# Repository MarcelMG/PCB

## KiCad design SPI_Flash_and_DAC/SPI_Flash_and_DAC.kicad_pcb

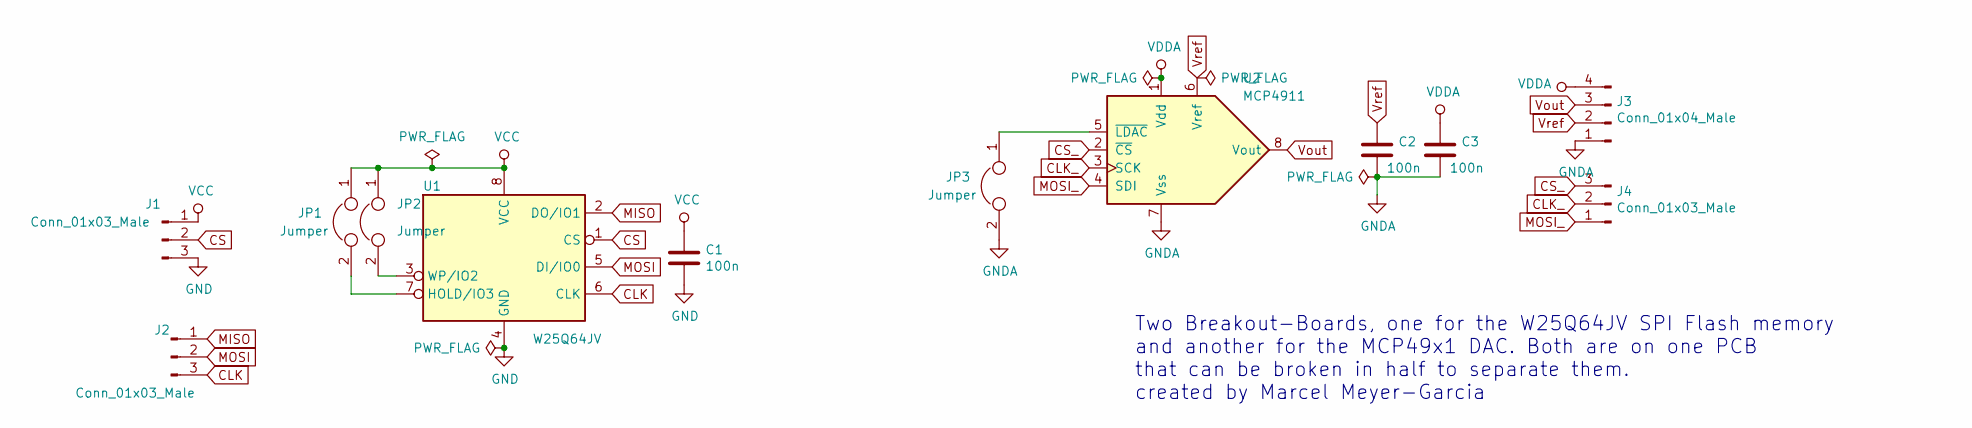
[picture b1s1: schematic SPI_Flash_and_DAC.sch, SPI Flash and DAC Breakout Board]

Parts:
C1, C2, C3: 100n; C_0805_2012Metric_Pad1.15x1.40mm_HandSolder
J1, J2, J4: Conn_01x03_Male; PinHeader_1x03_P2.54mm_Vertical
J3: Conn_01x04_Male; PinHeader_1x04_P2.54mm_Vertical
JP1, JP2, JP3: Jumper; SolderJumper-2_P1.3mm_Open_RoundedPad1.0x1.5mm
U1: W25Q64JV; SOIJ-8_5.3x5.3mm_P1.27mm
U2: MCP4911; SOIC-8_3.9x4.9mm_P1.27mm

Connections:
CLK: J2.3, U1.6 (CLK)
CLK_: J4.2, U2.3 (SCK)
CS: J1.2, U1.1 (CS)
CS_: J4.3, U2.2 (~CS)
GND: C1.2, J1.3, U1.4 (GND)
GNDA: C2.2, C3.2, J3.1, JP3.2, U2.7 (Vss)
MISO: J2.1, U1.2 (DO/IO1)
MOSI: J2.2, U1.5 (DI/IO0)
MOSI_: J4.1, U2.4 (SDI)
unnamed: JP1.2, U1.7 (HOLD/IO3)
unnamed: JP2.2, U1.3 (WP/IO2)
unnamed: JP3.1, U2.5 (~LDAC)
VCC: C1.1, J1.1, JP1.1, JP2.1, U1.8 (VCC)
VDDA: C3.1, J3.4, U2.1 (Vdd)
Vout: J3.3, U2.8 (Vout)
Vref: C2.1, J3.2, U2.6 (Vref)

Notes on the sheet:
Two Breakout-Boards, one for the W25Q64JV SPI Flash memory and another for the MCP49x1 DAC. Both are on one PCB that can be broken in half to separate them. created by Marcel Meyer-Garcia

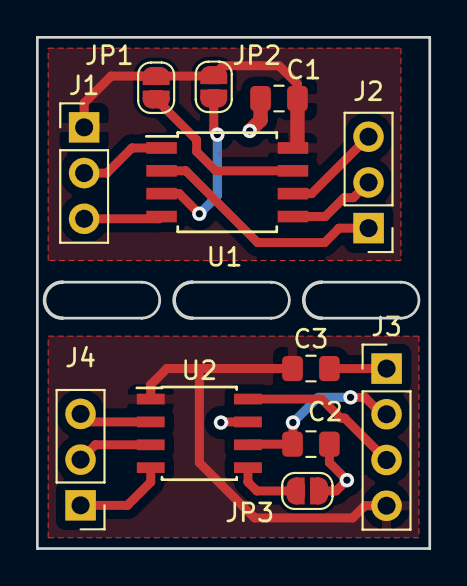
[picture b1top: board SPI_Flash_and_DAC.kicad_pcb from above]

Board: 2 copper layers, 21.7 x 28.4 mm, 12 parts (0 on the bottom side), 16 nets.
